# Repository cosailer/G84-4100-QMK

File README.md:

# G84-4100-QMK
A QMK compatible PCB for G84-4100 keyboard, it supports two PCB versions.

**specification:**\
mcu: atmega32u4\
width:99.06mm\
height:35.56mm

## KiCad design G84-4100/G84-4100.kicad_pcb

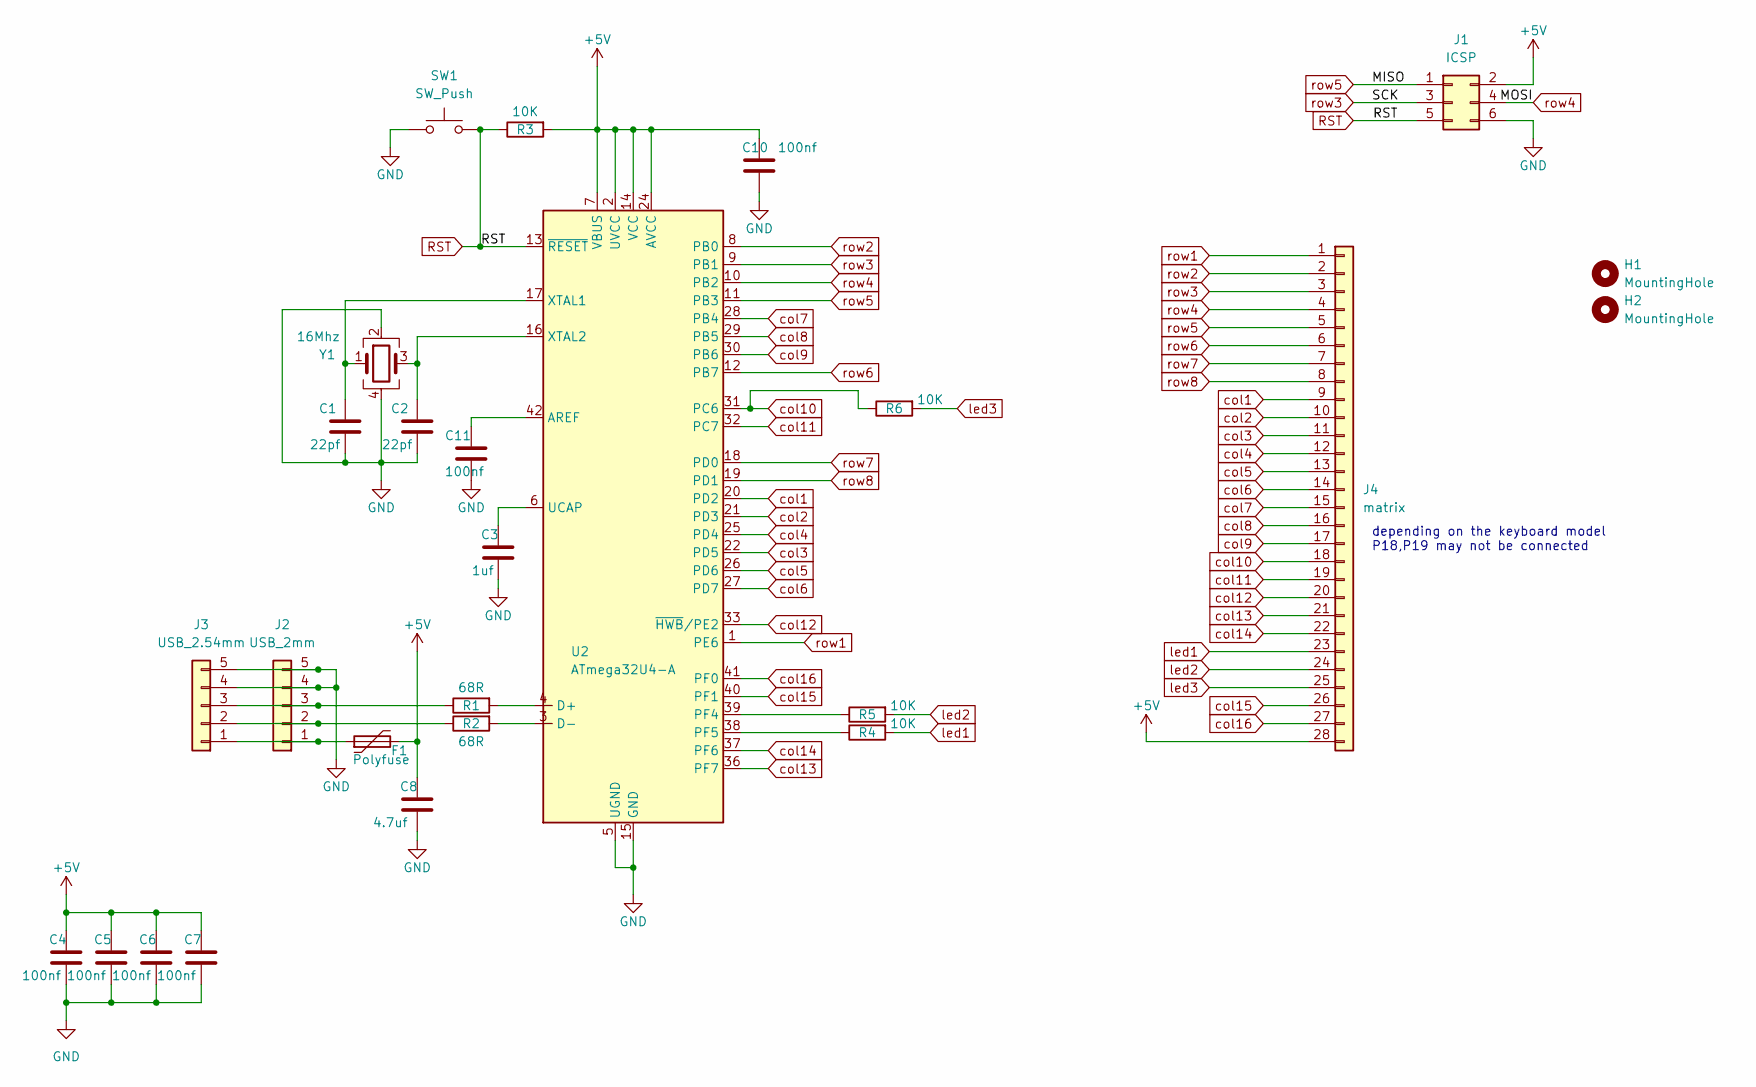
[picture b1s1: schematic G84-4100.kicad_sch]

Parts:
C1, C2: 22pf; C_0603_1608Metric_Pad1.08x0.95mm_HandSolder
C3: 1uf; C_0603_1608Metric_Pad1.08x0.95mm_HandSolder
C4, C5, C6, C7, C10, C11: 100nf; C_0603_1608Metric_Pad1.08x0.95mm_HandSolder
C8: 4.7uf; C_0603_1608Metric_Pad1.08x0.95mm_HandSolder
F1: Polyfuse; R_1210_3225Metric_Pad1.30x2.65mm_HandSolder
H1, H2: MountingHole; MountingHole_3.2mm_M3
J1: ICSP; PinHeader_2x03_P2.54mm_Vertical
J2: USB_2mm; PinHeader_1x05_P2.00mm_Vertical
J3: USB_2.54mm; PinHeader_1x05_P2.54mm_Vertical
J4: matrix; PinHeader_1x28_P1.27mm_Vertical
R1, R2: 68R; R_0603_1608Metric_Pad0.98x0.95mm_HandSolder
R3, R4, R5, R6: 10K; R_0603_1608Metric_Pad0.98x0.95mm_HandSolder
SW1: SW_Push; SW_SPST_Omron_B3FS-100xP
U2: ATmega32U4-A; QFN-44-1EP_7x7mm_P0.5mm_EP5.15x5.15mm_no_pad
Y1: 16Mhz; Crystal_SMD_3225-4Pin_3.2x2.5mm

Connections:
+5V: C4.1, C5.1, C6.1, C7.1, C8.1, C10.1, F1.2, J1.2, J4.28, R3.2, U2.2 (UVCC), U2.7 (VBUS), U2.14 (VCC), U2.24 (AVCC), U2.34 (VCC), U2.44 (AVCC)
GND: C1.2, C2.2, C3.2, C4.2, C5.2, C6.2, C7.2, C8.2, C10.2, C11.2, J1.6, J2.4, J2.5, J3.4, J3.5, SW1.1, U2.5 (UGND), U2.15 (GND), U2.23 (GND), U2.35 (GND), U2.43 (GND), Y1.2, Y1.4
unnamed: F1.1, J2.1, J3.1
unnamed: J2.2, J3.2, R2.1
unnamed: J2.3, J3.3, R1.1
unnamed: C11.1, U2.42 (AREF)
unnamed: R1.2, U2.4 (D+)
unnamed: R2.2, U2.3 (D-)
unnamed: R5.1, U2.39 (PF4)
unnamed: R4.1, U2.38 (PF5)
unnamed: C3.1, U2.6 (UCAP)
unnamed: C1.1, U2.17 (XTAL1), Y1.1
unnamed: C2.1, U2.16 (XTAL2), Y1.3
RST: J1.5, R3.1, SW1.2, U2.13 (~RESET)
col1: J4.9, U2.20 (PD2)
col2: J4.10, U2.21 (PD3)
col3: J4.11, U2.22 (PD5)
col4: J4.12, U2.25 (PD4)
col5: J4.13, U2.26 (PD6)
col6: J4.14, U2.27 (PD7)
col7: J4.15, U2.28 (PB4)
col8: J4.16, U2.29 (PB5)
col9: J4.17, U2.30 (PB6)
col10: J4.18, R6.1, U2.31 (PC6)
col11: J4.19, U2.32 (PC7)
col12: J4.20, U2.33 (~HWB/PE2)
col13: J4.21, U2.36 (PF7)
col14: J4.22, U2.37 (PF6)
col15: J4.26, U2.40 (PF1)
col16: J4.27, U2.41 (PF0)
led1: J4.23, R4.2
led2: J4.24, R5.2
led3: J4.25, R6.2
row1: J4.1, U2.1 (PE6)
row2: J4.2, U2.8 (PB0)
row3: J1.3, J4.3, U2.9 (PB1)
row4: J1.4, J4.4, U2.10 (PB2)
row5: J1.1, J4.5, U2.11 (PB3)
row6: J4.6, U2.12 (PB7)
row7: J4.7, U2.18 (PD0)
row8: J4.8, U2.19 (PD1)

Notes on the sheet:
depending on the keyboard model P18,P19 may not be connected

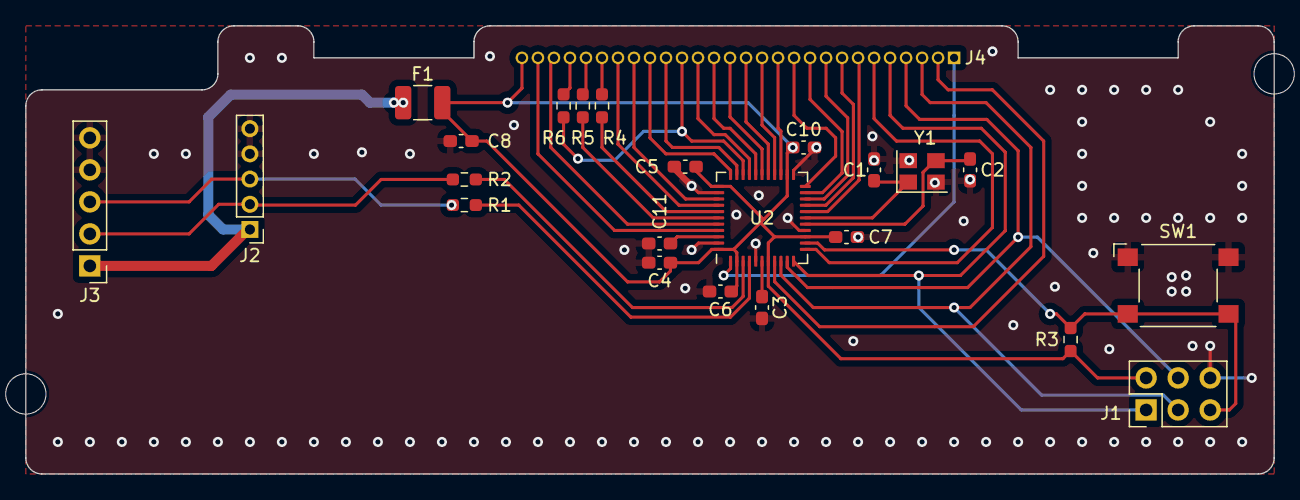
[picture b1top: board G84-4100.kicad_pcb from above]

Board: 2 copper layers, 99.1 x 35.6 mm, 26 parts (0 on the bottom side), 41 nets.

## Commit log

2023-10-21 add pcb
2023-10-24 add qmk source
